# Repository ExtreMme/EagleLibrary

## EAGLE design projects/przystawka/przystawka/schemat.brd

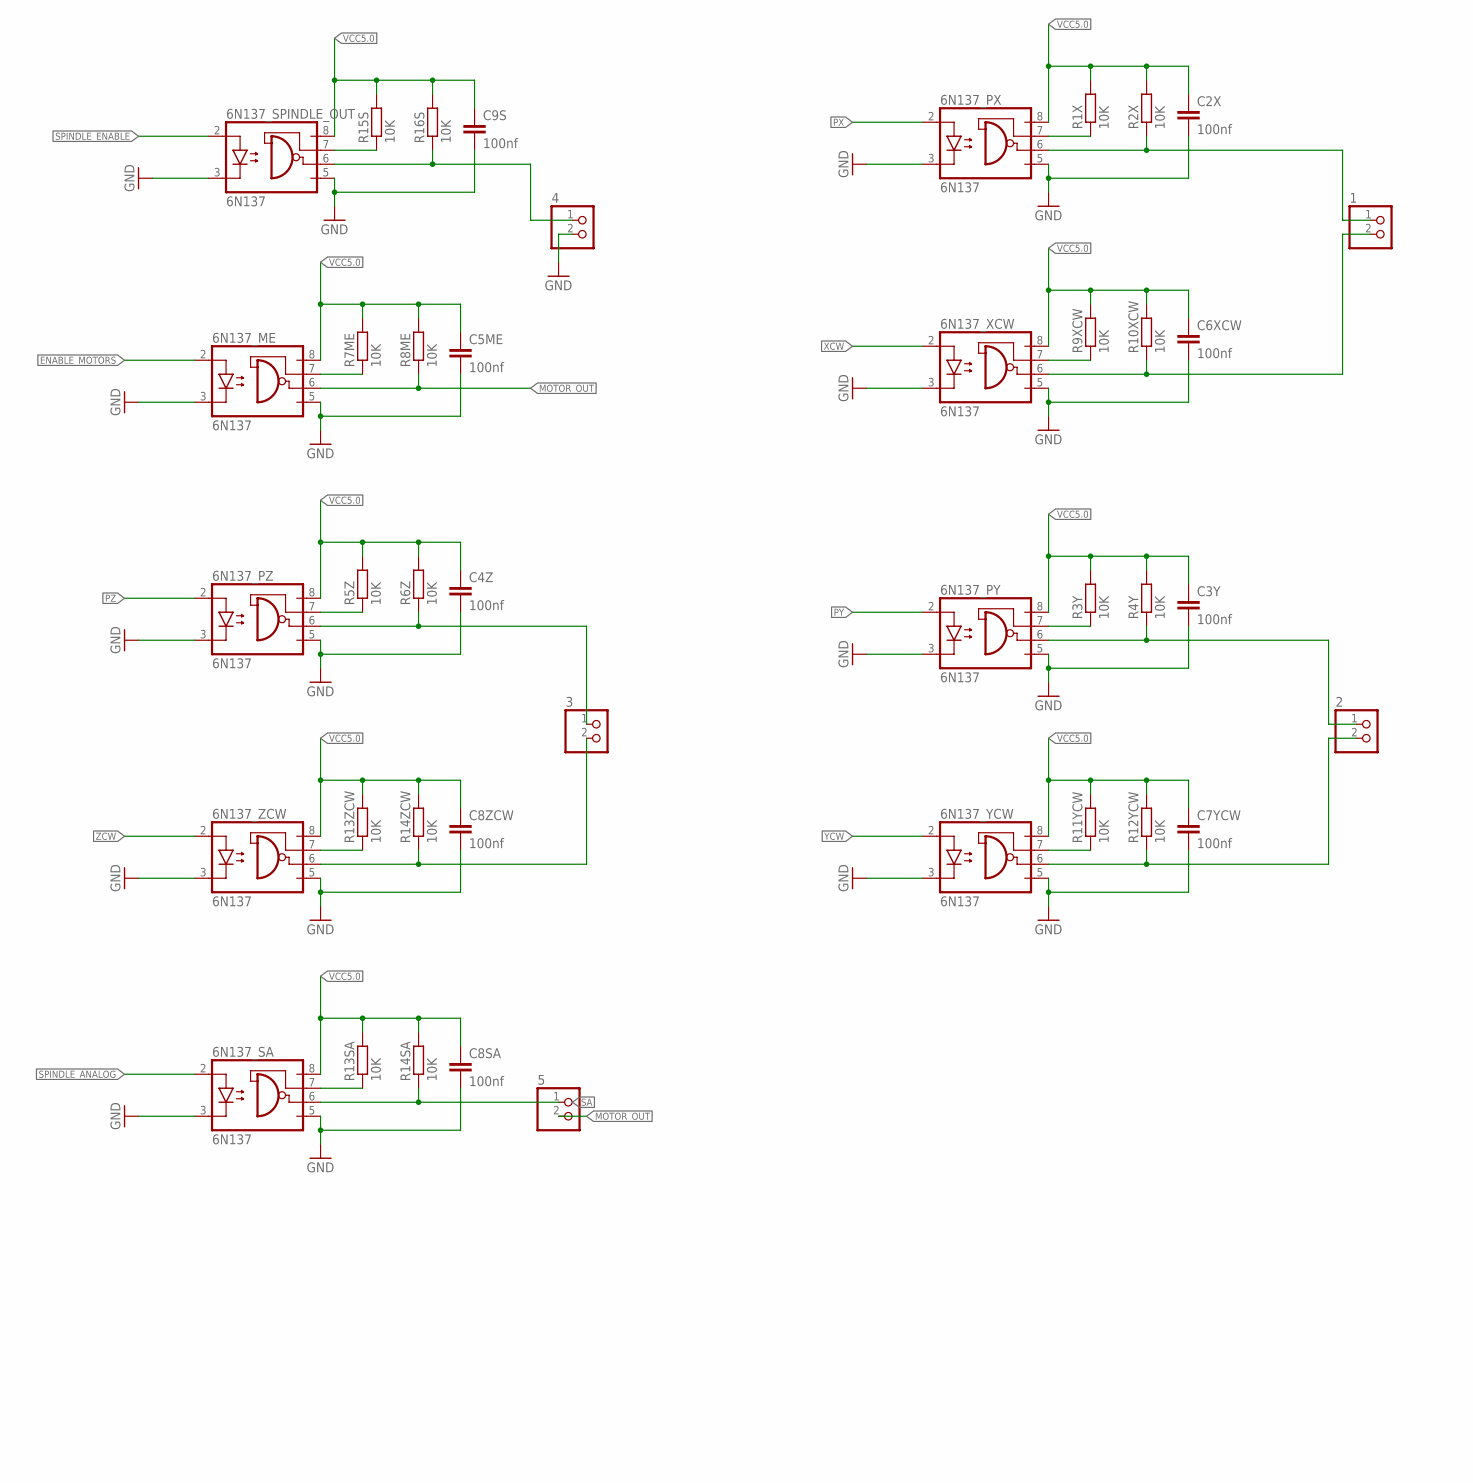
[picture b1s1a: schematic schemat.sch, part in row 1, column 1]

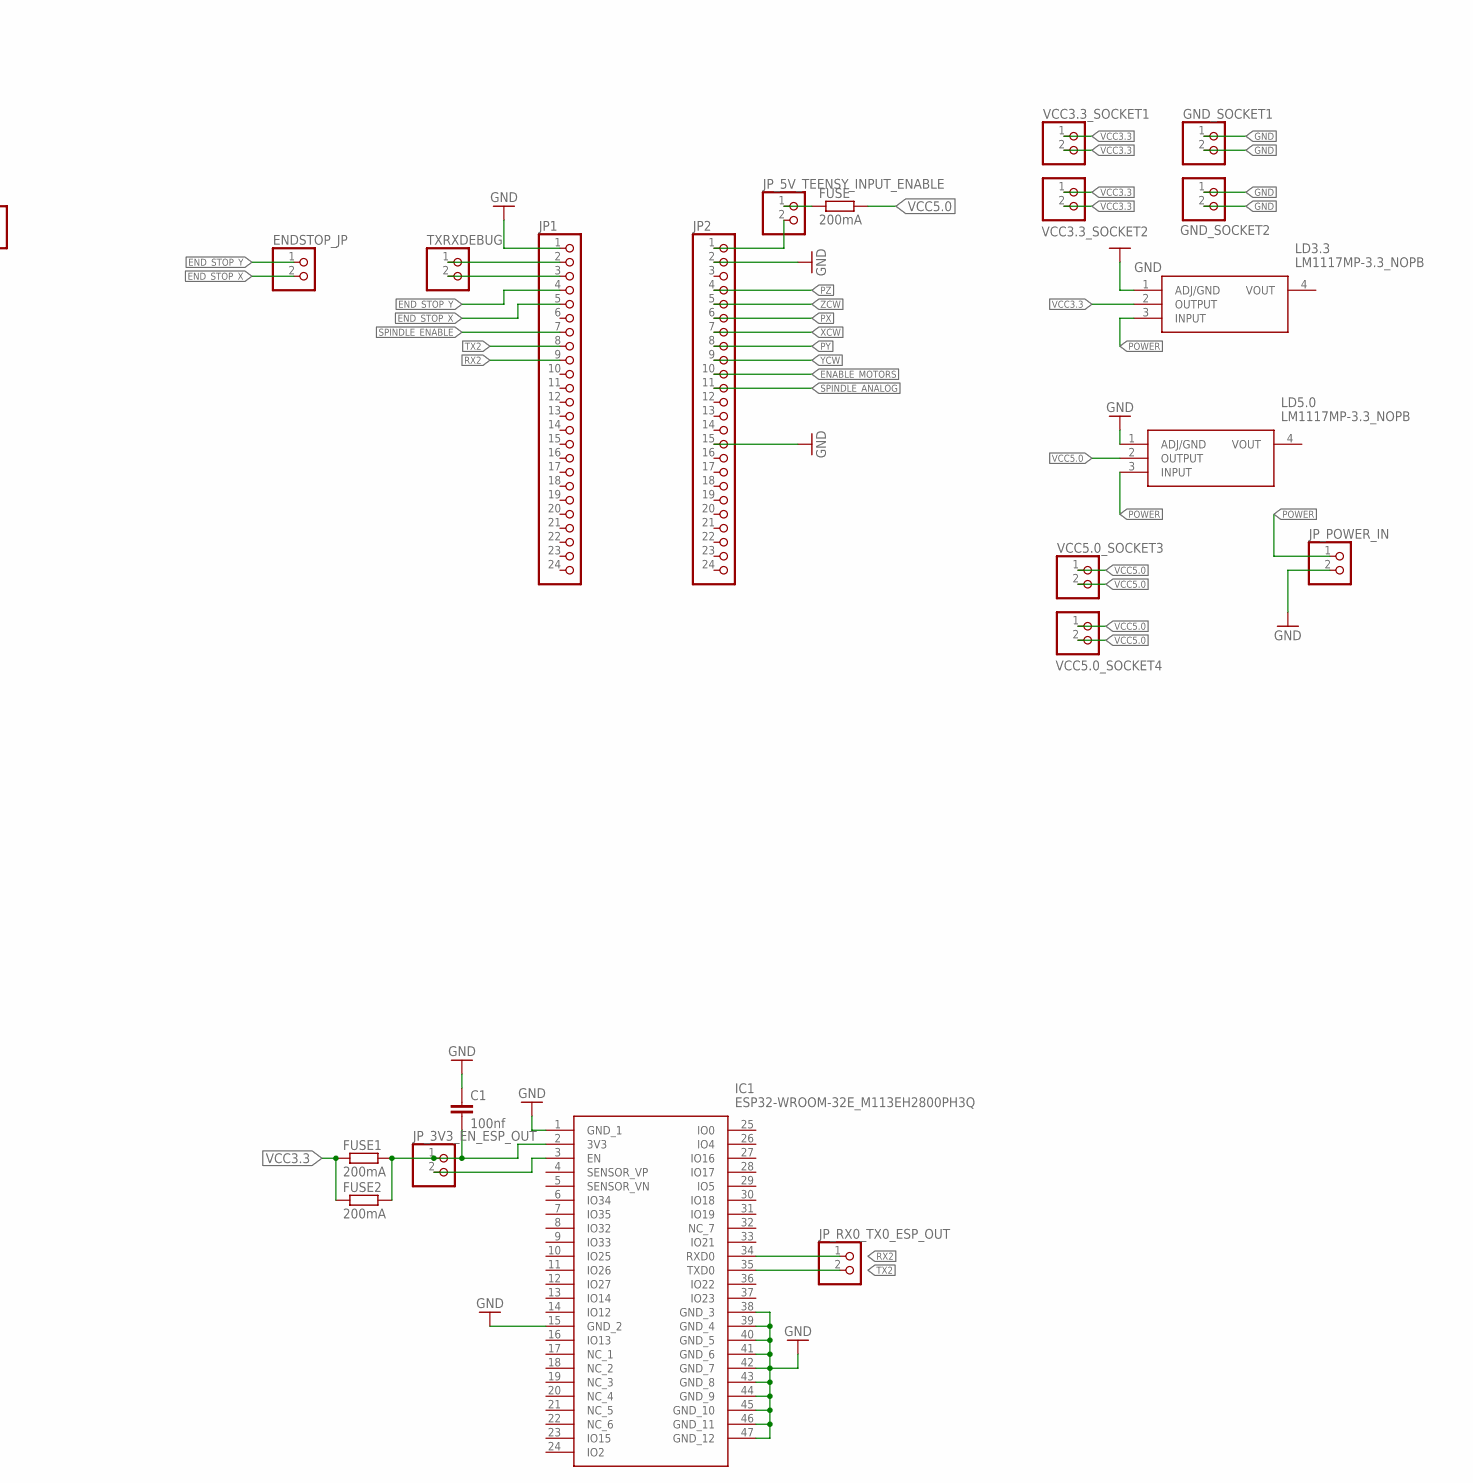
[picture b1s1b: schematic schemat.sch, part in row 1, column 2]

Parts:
1, 2, 3, 4, 5: PINHD-1X2; 1X02
6N137_ME, 6N137_PX, 6N137_PY, 6N137_PZ, 6N137_SA, 6N137_SPINDLE_OUT, 6N137_XCW, 6N137_YCW, 6N137_ZCW: 6N137; DIL08
C1, C2X, C3Y, C4Z, C5ME, C6XCW, C7YCW, C8SA, C8ZCW, C9S: 100nf; C0805
ENDSTOP_JP: PINHD-1X2; 1X02
FUSE, FUSE1, FUSE2: 200mA; R2512
GND_SOCKET1, GND_SOCKET2: PINHD-1X2; 1X02
IC1: ESP32-WROOM-32E_M113EH2800PH3Q; ESP32WROOM32EM113EH2800PH3Q0
JP1, JP2: PINHD-1X24; 1X24
JP_3V3_EN_ESP_OUT, JP_5V_TEENSY_INPUT_ENABLE: PINHD-1X2; 1X02
JP_POWER_IN: PINHD-1X2; 1X02
JP_RX0_TX0_ESP_OUT: PINHD-1X2; 1X02
LD3.3, LD5.0: LM1117MP-3.3_NOPB; SOT230P700X180-4N
R1X, R2X, R3Y, R4Y, R5Z, R6Z, R7ME, R8ME, R9XCW, R10XCW, R11YCW, R12YCW, R13SA, R13ZCW, R14SA, R14ZCW, R15S, R16S: 10K; R0805
TXRXDEBUG: PINHD-1X2; 1X02
VCC3.3_SOCKET1, VCC3.3_SOCKET2, VCC5.0_SOCKET3, VCC5.0_SOCKET4: PINHD-1X2; 1X02

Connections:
ENABLE_MOTORS: 6N137_ME.2 (A), JP2.10
END_STOP_X: ENDSTOP_JP.2, JP1.5
END_STOP_Y: ENDSTOP_JP.1, JP1.4
GND: 4.2, 6N137_ME.3 (C), 6N137_ME.5 (GND), 6N137_PX.3 (C), 6N137_PX.5 (GND), 6N137_PY.3 (C), 6N137_PY.5 (GND), 6N137_PZ.3 (C), 6N137_PZ.5 (GND), 6N137_SA.3 (C), 6N137_SA.5 (GND), 6N137_SPINDLE_OUT.3 (C), 6N137_SPINDLE_OUT.5 (GND), 6N137_XCW.3 (C), 6N137_XCW.5 (GND), 6N137_YCW.3 (C), 6N137_YCW.5 (GND), 6N137_ZCW.3 (C), 6N137_ZCW.5 (GND), C1.1, C2X.2, C3Y.2, C4Z.2, C5ME.2, C6XCW.2, C7YCW.2, C8SA.2, C8ZCW.2, C9S.2, GND_SOCKET1.1, GND_SOCKET1.2, GND_SOCKET2.1, GND_SOCKET2.2, IC1.1 (GND_1), IC1.15 (GND_2), IC1.38 (GND_3), IC1.39 (GND_4), IC1.40 (GND_5), IC1.41 (GND_6), IC1.42 (GND_7), IC1.43 (GND_8), IC1.44 (GND_9), IC1.45 (GND_10), IC1.46 (GND_11), IC1.47 (GND_12), JP1.1, JP2.2, JP2.15, JP_POWER_IN.2, LD3.3.1 (ADJ/GND), LD5.0.1 (ADJ/GND)
MOTOR_OUT: 5.2, 6N137_ME.6 (VO), R8ME.1
unnamed: JP2.1, JP_5V_TEENSY_INPUT_ENABLE.2
unnamed: JP1.2, TXRXDEBUG.1
unnamed: IC1.3 (EN), JP_3V3_EN_ESP_OUT.2
unnamed: JP1.3, TXRXDEBUG.2
unnamed: 6N137_PX.7 (VE), R1X.1
unnamed: 6N137_PY.7 (VE), R3Y.1
unnamed: 6N137_PZ.7 (VE), R5Z.1
unnamed: 6N137_ME.7 (VE), R7ME.1
unnamed: 6N137_SPINDLE_OUT.7 (VE), R15S.1
unnamed: 6N137_XCW.7 (VE), R9XCW.1
unnamed: 6N137_YCW.7 (VE), R11YCW.1
unnamed: 6N137_ZCW.7 (VE), R13ZCW.1
unnamed: FUSE.1, JP_5V_TEENSY_INPUT_ENABLE.1
unnamed: C1.2, FUSE1.2, FUSE2.2, IC1.2 (3V3), JP_3V3_EN_ESP_OUT.1
unnamed: 6N137_SA.7 (VE), R13SA.1
POWER: JP_POWER_IN.1, LD3.3.3 (INPUT), LD5.0.3 (INPUT)
PX: 6N137_PX.2 (A), JP2.6
PX_OUT: 1.1, 6N137_PX.6 (VO), R2X.1
PY: 6N137_PY.2 (A), JP2.8
PY_OUT: 2.1, 6N137_PY.6 (VO), R4Y.1
PZ: 6N137_PZ.2 (A), JP2.4
PZ_OUT: 3.1, 6N137_PZ.6 (VO), R6Z.1
RX2: IC1.34 (RXD0), JP1.9, JP_RX0_TX0_ESP_OUT.1
SA: 5.1, 6N137_SA.6 (VO), R14SA.1
SPINDLE_ANALOG: 6N137_SA.2 (A), JP2.11
SPINDLE_ENABLE: 6N137_SPINDLE_OUT.2 (A), JP1.7
SPINDLE_OUT: 4.1, 6N137_SPINDLE_OUT.6 (VO), R16S.1
TX2: IC1.35 (TXD0), JP1.8, JP_RX0_TX0_ESP_OUT.2
VCC3.3: FUSE1.1, FUSE2.1, LD3.3.2 (OUTPUT), VCC3.3_SOCKET1.1, VCC3.3_SOCKET1.2, VCC3.3_SOCKET2.1, VCC3.3_SOCKET2.2
VCC5.0: 6N137_ME.8 (VCC), 6N137_PX.8 (VCC), 6N137_PY.8 (VCC), 6N137_PZ.8 (VCC), 6N137_SA.8 (VCC), 6N137_SPINDLE_OUT.8 (VCC), 6N137_XCW.8 (VCC), 6N137_YCW.8 (VCC), 6N137_ZCW.8 (VCC), C2X.1, C3Y.1, C4Z.1, C5ME.1, C6XCW.1, C7YCW.1, C8SA.1, C8ZCW.1, C9S.1, FUSE.2, LD5.0.2 (OUTPUT), R1X.2, R2X.2, R3Y.2, R4Y.2, R5Z.2, R6Z.2, R7ME.2, R8ME.2, R9XCW.2, R10XCW.2, R11YCW.2, R12YCW.2, R13SA.2, R13ZCW.2, R14SA.2, R14ZCW.2, R15S.2, R16S.2, VCC5.0_SOCKET3.1, VCC5.0_SOCKET3.2, VCC5.0_SOCKET4.1, VCC5.0_SOCKET4.2
XCW: 6N137_XCW.2 (A), JP2.7
XCW_OUT: 1.2, 6N137_XCW.6 (VO), R10XCW.1
YCW: 6N137_YCW.2 (A), JP2.9
YCW_OUT: 2.2, 6N137_YCW.6 (VO), R12YCW.1
ZCW: 6N137_ZCW.2 (A), JP2.5
ZCW_OUT: 3.2, 6N137_ZCW.6 (VO), R14ZCW.1

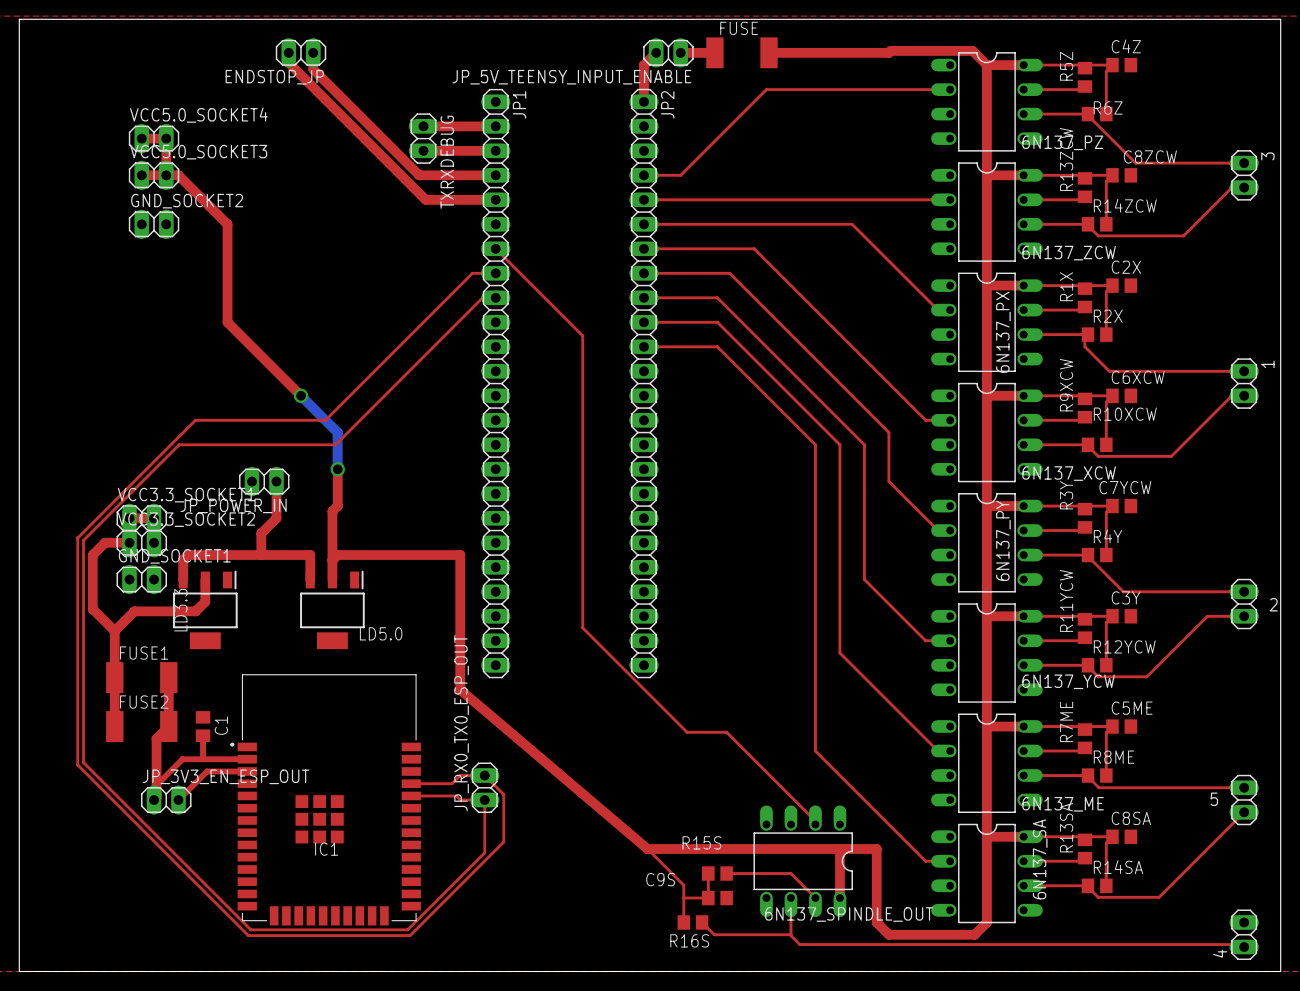
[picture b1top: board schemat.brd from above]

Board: 2 copper layers, 130.8 x 98.7 mm, 62 parts (0 on the bottom side), 41 nets.

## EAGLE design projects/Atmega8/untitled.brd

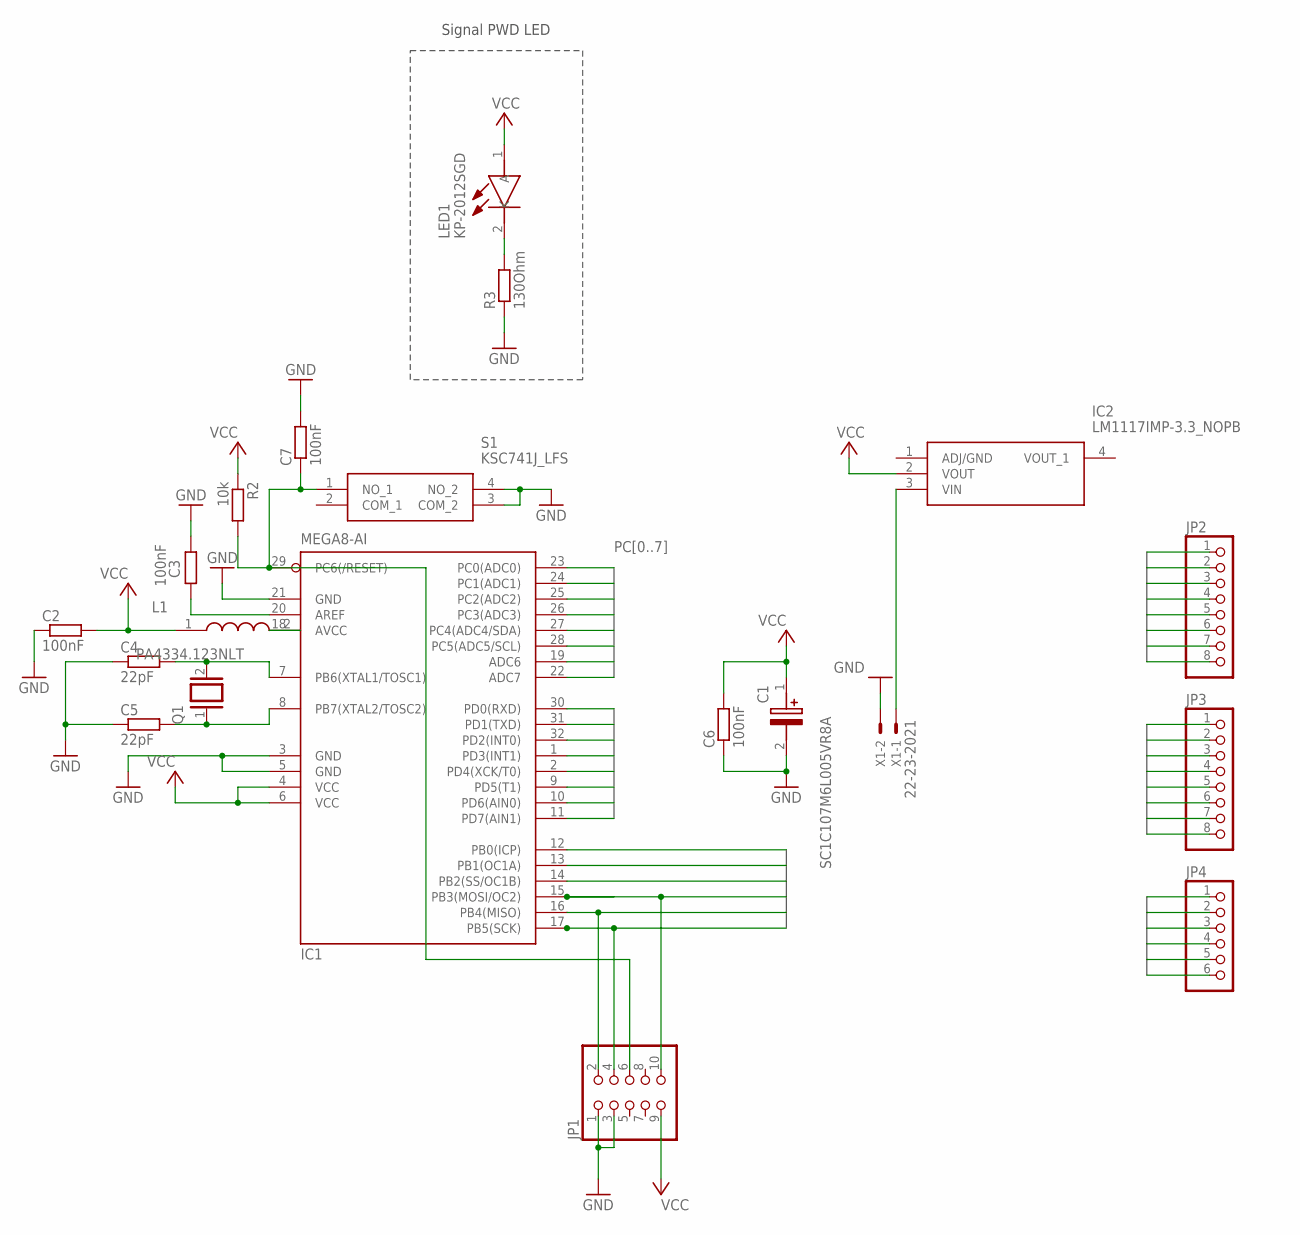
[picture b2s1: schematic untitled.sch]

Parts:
C1: SC1C107M6L005VR8A; CAPAE660X560N
C2, C3, C6, C7: 100nF; R0805
C4, C5: 22pF; R0805
IC1: MEGA8-AI; TQFP32-08
IC2: LM1117IMP-3.3_NOPB; SOT230P700X180-4N
JP1: PINHD-2X5; 2X05
JP2, JP3: PINHD-1X8; 1X08
JP4: PINHD-1X6; 1X06
L1: PA4334.123NLT; PA4334123NLT
LED1: KP-2012SGD; KP2012SGD
Q1: XTAL/S; QS
R2: 10k; R0805
R3: 130Ohm; R0805
S1: KSC741J_LFS; KSC821JOLLFS
X1: 22-23-2021

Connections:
ADJ/GND: IC2.1 (ADJ/GND)
GND: C1.2 (-), C2.1, C3.1, C4.1, C5.1, C6.1, C7.2, IC1.3 (GND), IC1.5 (GND), IC1.21 (GND), JP1.1, JP1.3, R3.1, S1.3 (COM_2), S1.4 (NO_2), X1.2
unnamed: C7.1, IC1.29 (PC6(/RESET)), JP1.6, R2.2, S1.1 (NO_1)
unnamed: IC1.18 (AVCC), L1.2
unnamed: C3.2, IC1.20 (AREF)
unnamed: C4.2, IC1.7 (PB6(XTAL1/TOSC1)), Q1.2
unnamed: C5.2, IC1.8 (PB7(XTAL2/TOSC2)), Q1.1
unnamed: LED1.2 (K), R3.2
unnamed: IC2.3 (VIN), X1.1
PB0: IC1.12 (PB0(ICP)), JP4.1
PB1: IC1.13 (PB1(OC1A)), JP4.2
PB2: IC1.14 (PB2(SS/OC1B)), JP4.3
PB3: IC1.15 (PB3(MOSI/OC2)), JP1.10, JP4.4
PB4: IC1.16 (PB4(MISO)), JP1.2, JP4.5
PB5: IC1.17 (PB5(SCK)), JP1.4, JP4.6
PC0: IC1.23 (PC0(ADC0)), JP2.1
PC1: IC1.24 (PC1(ADC1)), JP2.2
PC2: IC1.25 (PC2(ADC2)), JP2.3
PC3: IC1.26 (PC3(ADC3)), JP2.4
PC4: IC1.27 (PC4(ADC4/SDA)), JP2.5
PC5: IC1.28 (PC5(ADC5/SCL)), JP2.6
PC6: IC1.19 (ADC6), JP2.7
PC7: IC1.22 (ADC7), JP2.8
PD0: IC1.30 (PD0(RXD)), JP3.1
PD1: IC1.31 (PD1(TXD)), JP3.2
PD2: IC1.32 (PD2(INT0)), JP3.3
PD3: IC1.1 (PD3(INT1)), JP3.4
PD4: IC1.2 (PD4(XCK/T0)), JP3.5
PD5: IC1.9 (PD5(T1)), JP3.6
PD6: IC1.10 (PD6(AIN0)), JP3.7
PD7: IC1.11 (PD7(AIN1)), JP3.8
VCC: C1.1 (+), C2.2, C6.2, IC1.4 (VCC), IC1.6 (VCC), IC2.2 (VOUT), JP1.9, L1.1, LED1.1 (A), R2.1

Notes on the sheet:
Signal PWD LED

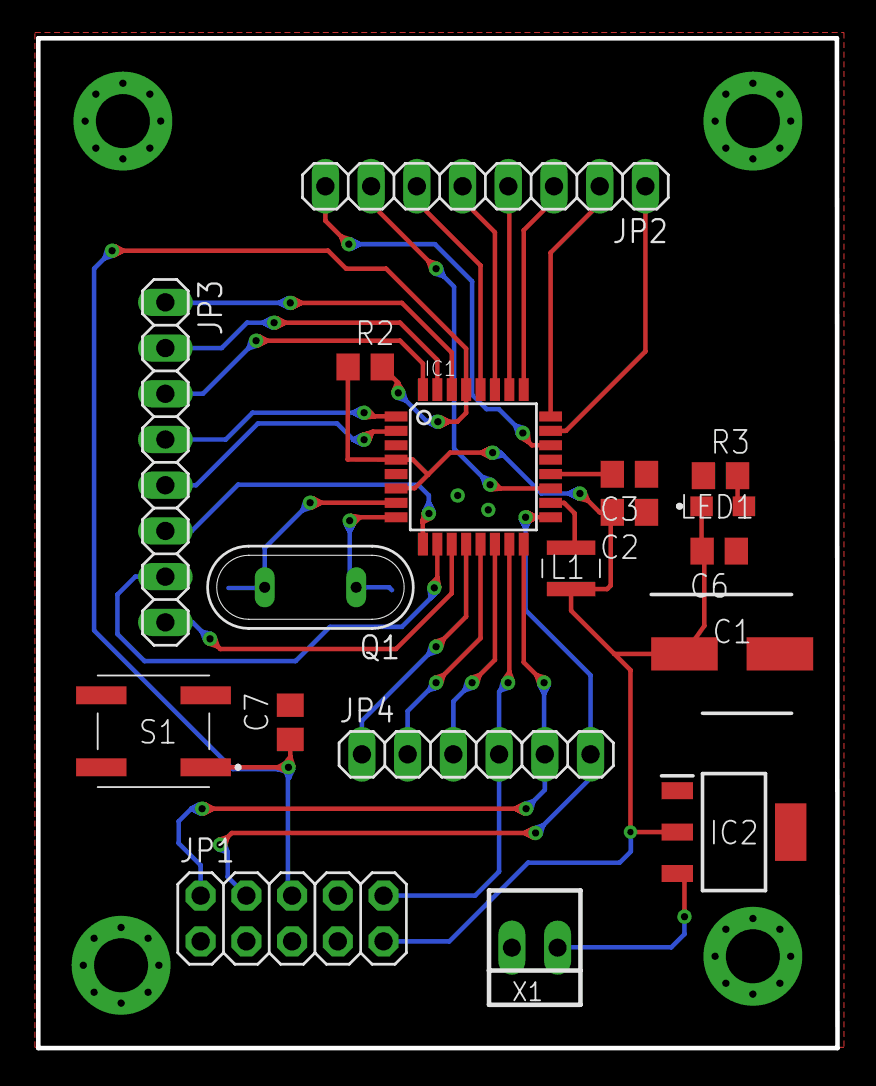
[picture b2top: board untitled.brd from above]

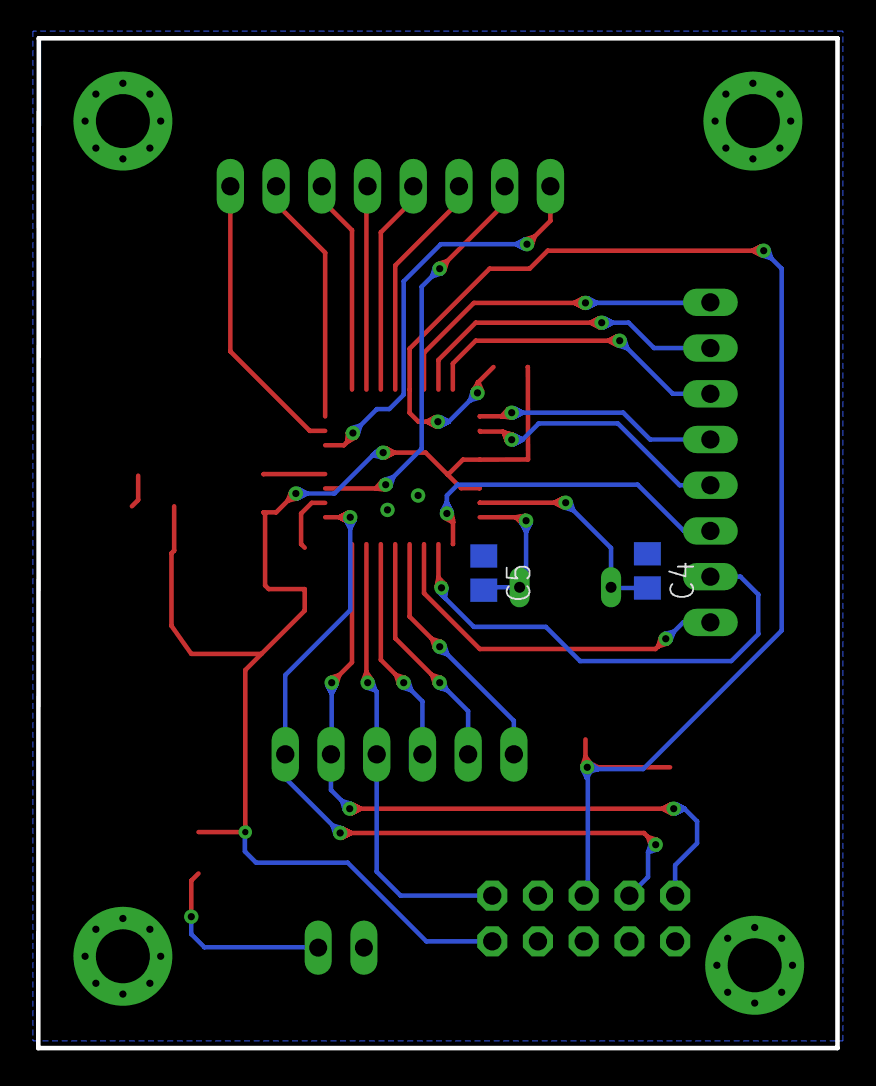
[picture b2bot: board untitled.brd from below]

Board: 2 copper layers, 44.4 x 56.1 mm, 20 parts (2 on the bottom side), 31 nets.

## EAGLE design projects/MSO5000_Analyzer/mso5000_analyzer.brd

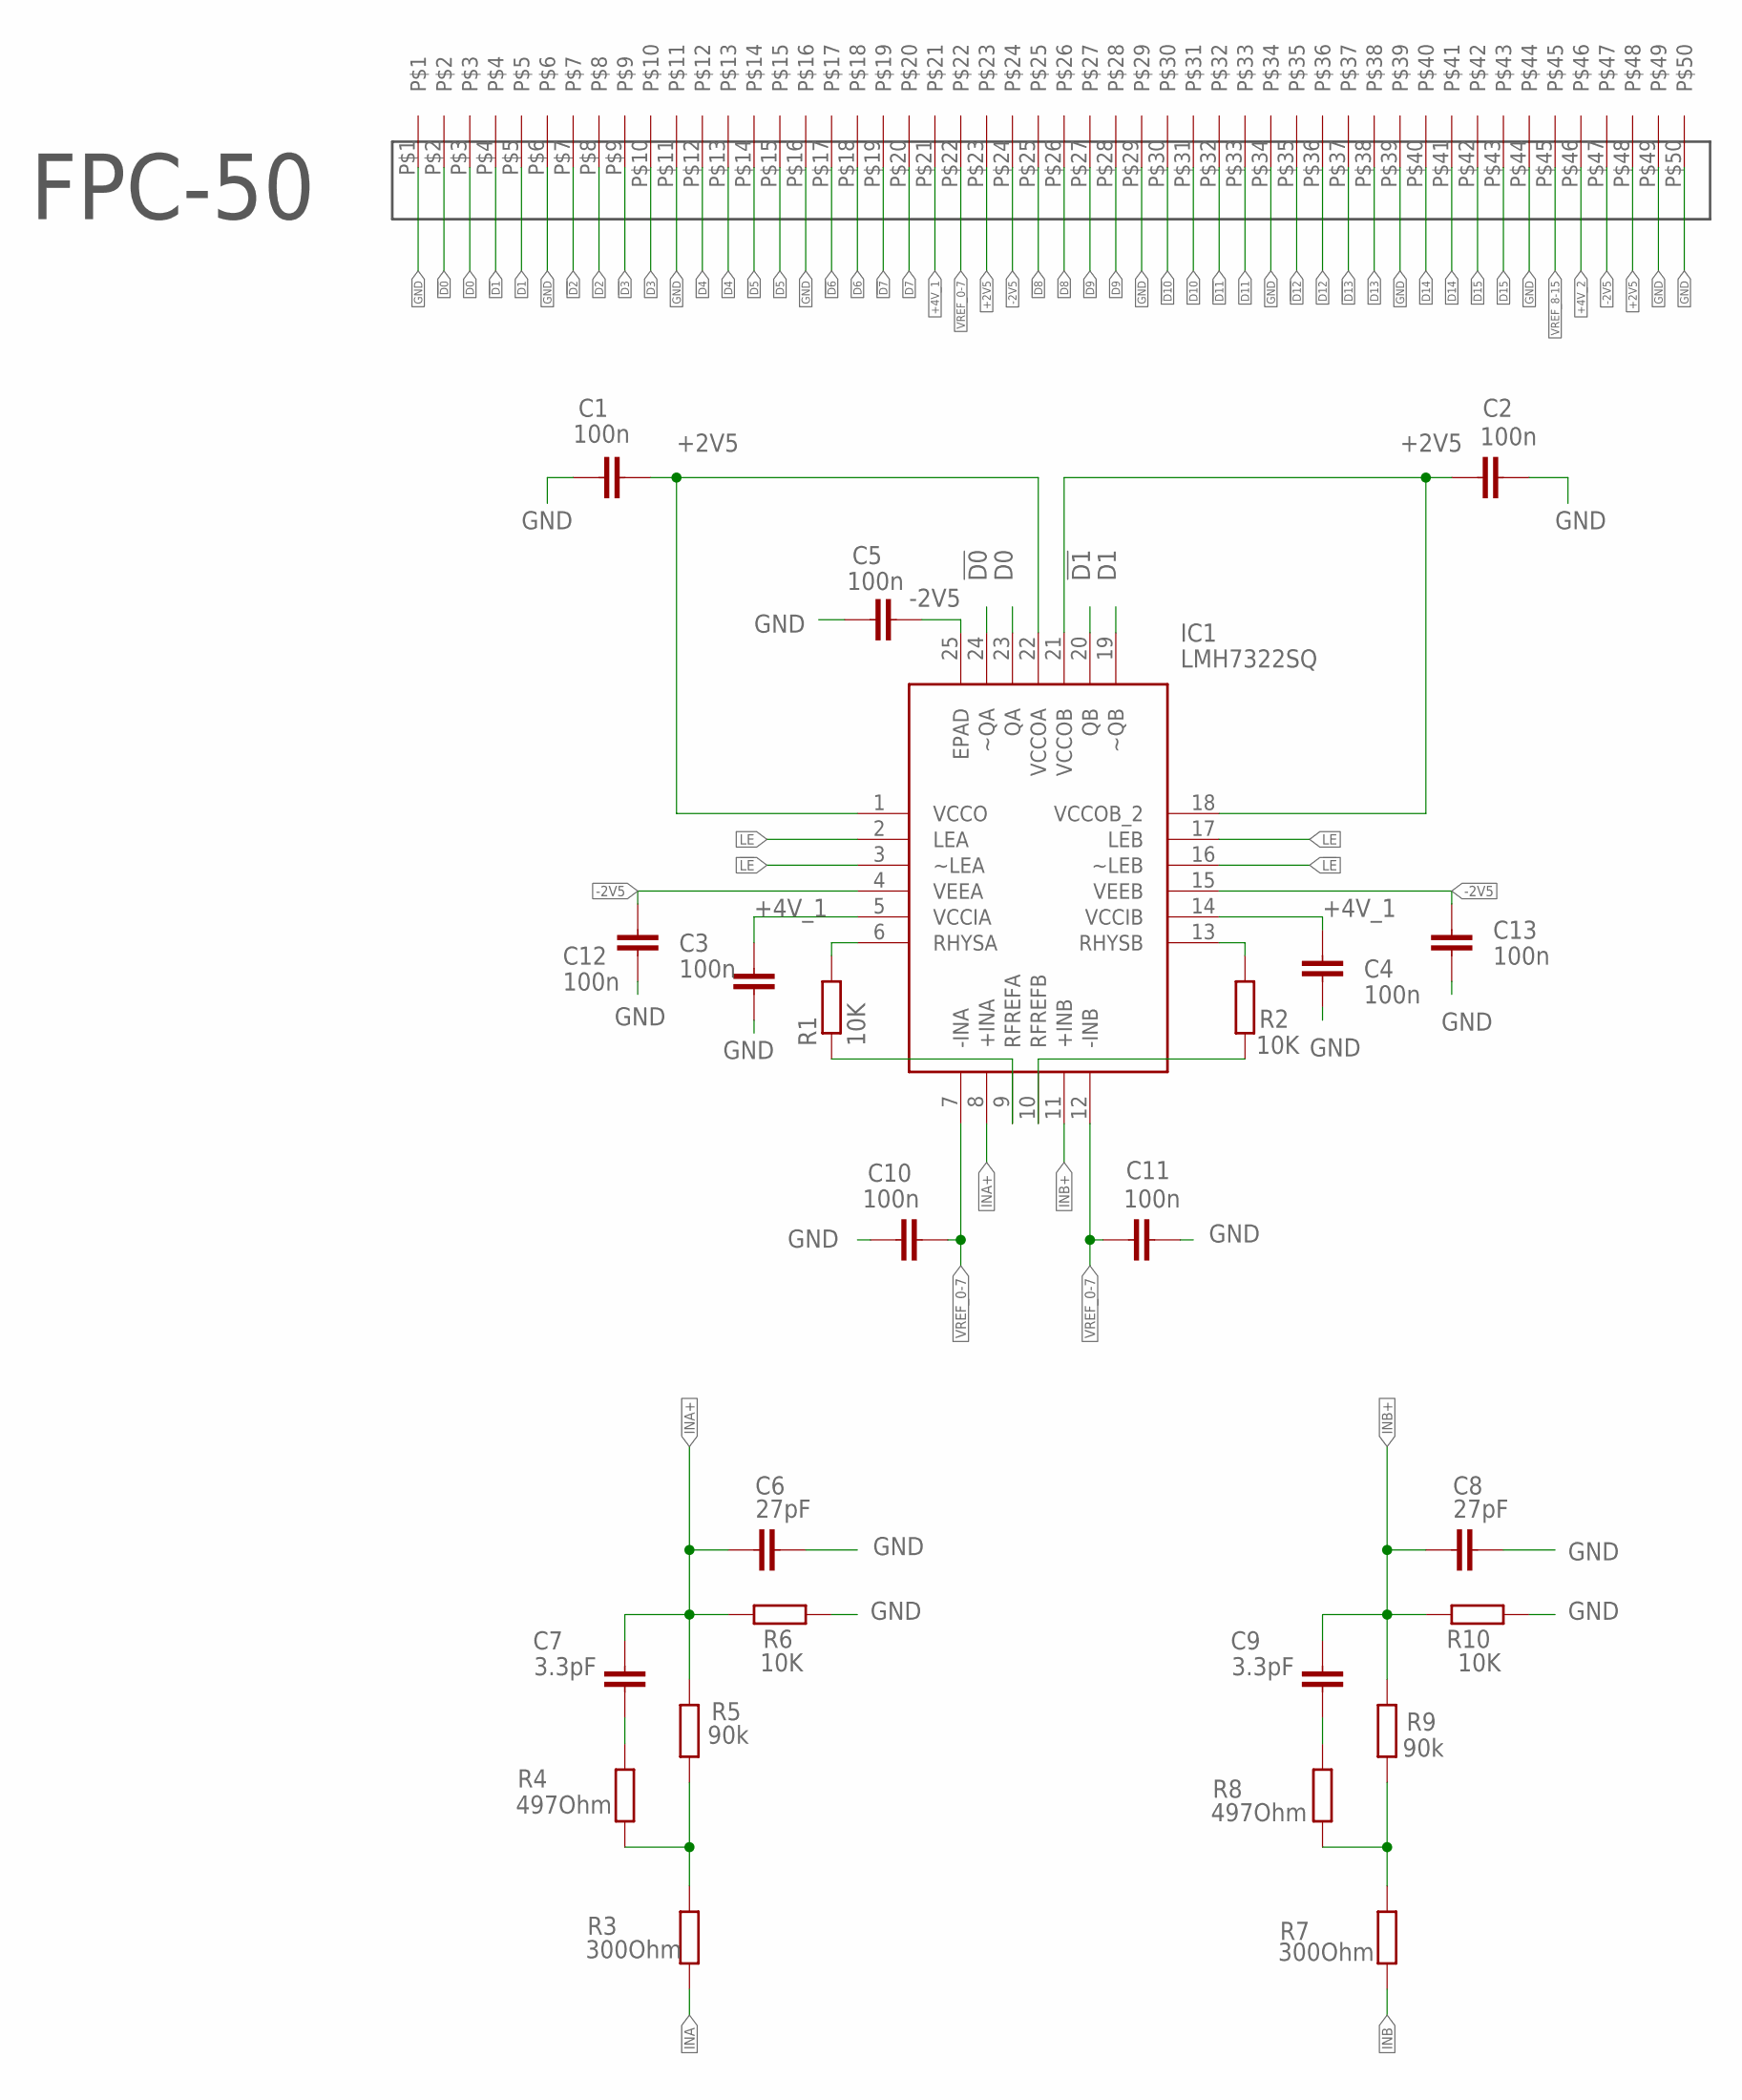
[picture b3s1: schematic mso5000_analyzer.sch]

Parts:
C1, C2, C3, C4, C5, C10, C11, C12, C13: 100n; C0805
C6, C8: 27pF; C0805
C7, C9: 3.3pF; C0805
FPC-50: ZIFF-050
IC1: LMH7322SQ; QFN50P400X400X80-25N
R1, R2, R6, R10: 10K; R0805
R3, R7: 300Ohm; R0805
R4, R8: 497Ohm; R0805
R5, R9: 90k; R0805

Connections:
!D0: FPC-50.P$2, IC1.24 (~QA)
!D1: FPC-50.P$4, IC1.20 (QB)
!D2: FPC-50.P$7
!D3: FPC-50.P$9
!D4: FPC-50.P$12
!D5: FPC-50.P$14
!D6: FPC-50.P$17
!D7: FPC-50.P$19
!D8: FPC-50.P$25
!D9: FPC-50.P$27
!D10: FPC-50.P$30
!D11: FPC-50.P$32
!D12: FPC-50.P$35
!D13: FPC-50.P$37
!D14: FPC-50.P$40
!D15: FPC-50.P$42
!LE: IC1.3 (~LEA), IC1.16 (~LEB)
+2V5: C1.1, C2.2, FPC-50.P$23, FPC-50.P$48, IC1.1 (VCCO), IC1.18 (VCCOB_2), IC1.21 (VCCOB), IC1.22 (VCCOA)
+4V_1: C3.1, C4.1, FPC-50.P$21, IC1.5 (VCCIA), IC1.14 (VCCIB)
+4V_2: FPC-50.P$46
-2V5: C5.1, C12.1, C13.1, FPC-50.P$24, FPC-50.P$47, IC1.4 (VEEA), IC1.15 (VEEB), IC1.25 (EPAD)
D0: FPC-50.P$3, IC1.23 (QA)
D1: FPC-50.P$5, IC1.19 (~QB)
D2: FPC-50.P$8
D3: FPC-50.P$10
D4: FPC-50.P$13
D5: FPC-50.P$15
D6: FPC-50.P$18
D7: FPC-50.P$20
D8: FPC-50.P$26
D9: FPC-50.P$28
D10: FPC-50.P$31
D11: FPC-50.P$33
D12: FPC-50.P$36
D13: FPC-50.P$38
D14: FPC-50.P$41
D15: FPC-50.P$43
GND: C1.2, C2.1, C3.2, C4.2, C5.2, C6.2, C8.2, C10.1, C11.2, C12.2, C13.2, FPC-50.P$1, FPC-50.P$6, FPC-50.P$11, FPC-50.P$16, FPC-50.P$29, FPC-50.P$34, FPC-50.P$39, FPC-50.P$44, FPC-50.P$49, FPC-50.P$50, R6.1, R10.1
INA: R3.1
INA+: C6.1, C7.2, IC1.8 (+INA), R5.2, R6.2
INB: R7.1
INB+: C8.1, C9.2, IC1.11 (+INB), R9.2, R10.2
LE: IC1.2 (LEA), IC1.17 (LEB)
unnamed: IC1.10 (RFREFB), R2.1
unnamed: R3.2, R4.1, R5.1
unnamed: IC1.6 (RHYSA), R1.2
unnamed: IC1.9 (RFREFA), R1.1
unnamed: IC1.13 (RHYSB), R2.2
unnamed: C7.1, R4.2
unnamed: R7.2, R8.1, R9.1
unnamed: C9.1, R8.2
VREF_0-7: C10.2, C11.1, FPC-50.P$22, IC1.7 (-INA), IC1.12 (-INB)
VREF_8-15: FPC-50.P$45

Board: 2 copper layers, 25 parts (0 on the bottom side), 21 nets, no tracks yet.

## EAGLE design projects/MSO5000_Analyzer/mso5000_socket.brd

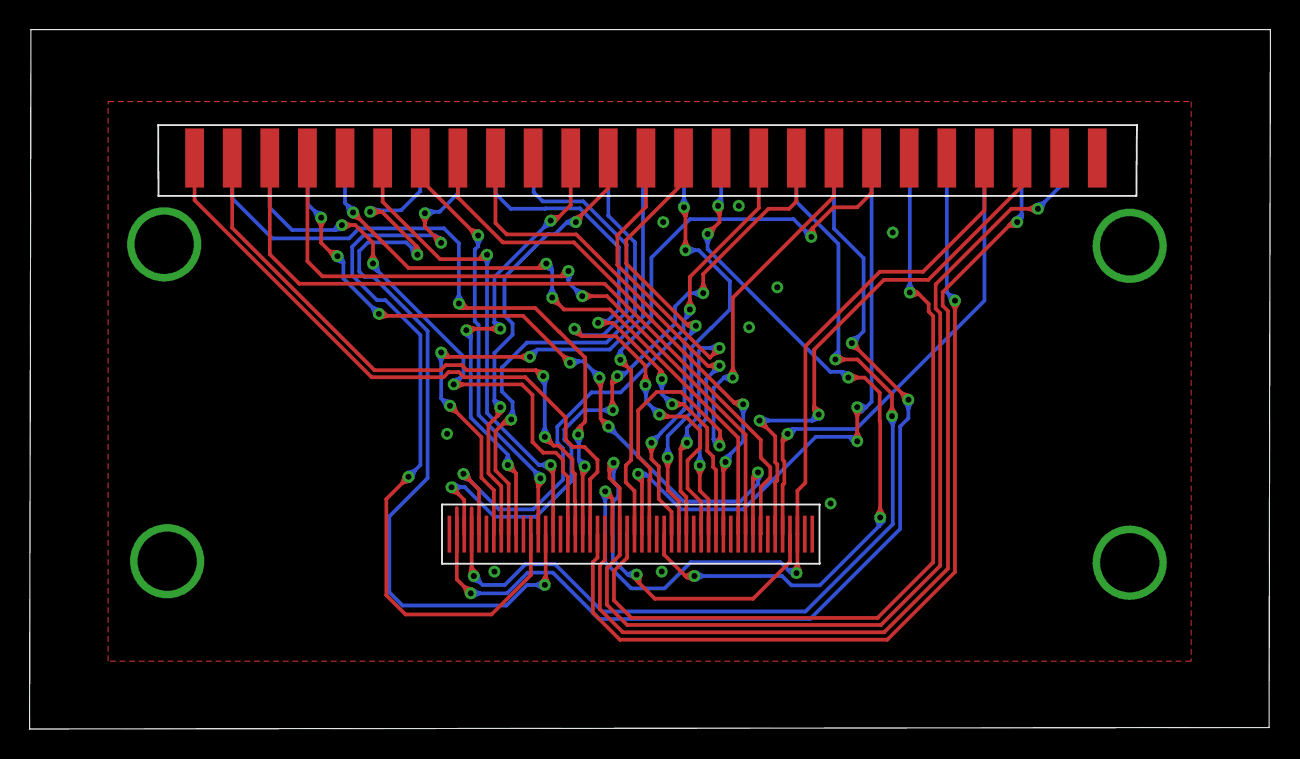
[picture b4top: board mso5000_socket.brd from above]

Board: 2 copper layers, 83.8 x 47.2 mm, 3 parts (1 on the bottom side), 39 nets.

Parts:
IDC_BOTTOM: 1X25_IDC_PADS
IDC_TOP: 1X25_IDC_PADS
U$3: ZIFF-050

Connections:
!D0: IDC_BOTTOM.P$18, U$3.P$2
!D1: IDC_BOTTOM.P$17, U$3.P$4
!D2: IDC_BOTTOM.P$13, U$3.P$7
!D3: IDC_BOTTOM.P$12, U$3.P$9
!D4: IDC_BOTTOM.P$8, U$3.P$12
!D5: IDC_BOTTOM.P$7, U$3.P$14
!D6: IDC_BOTTOM.P$3, U$3.P$17
!D7: IDC_BOTTOM.P$2, U$3.P$19
!D8: IDC_BOTTOM.P$20, U$3.P$25
!D9: IDC_BOTTOM.P$19, U$3.P$27
!D10: IDC_BOTTOM.P$15, U$3.P$30
!D11: IDC_BOTTOM.P$14, U$3.P$32
!D12: IDC_BOTTOM.P$10, U$3.P$35
!D13: IDC_BOTTOM.P$9, U$3.P$37
!D14: IDC_BOTTOM.P$5, U$3.P$40
!D15: IDC_BOTTOM.P$4, U$3.P$42
+2V5: IDC_TOP.P$22, U$3.P$23, U$3.P$48
+4V_1: IDC_BOTTOM.P$21, U$3.P$21
+4V_2: IDC_BOTTOM.P$22, U$3.P$46
-2V5: IDC_BOTTOM.P$24, U$3.P$24, U$3.P$47
D0: IDC_TOP.P$17, U$3.P$3
D1: IDC_TOP.P$16, U$3.P$5
D2: IDC_TOP.P$12, U$3.P$8
D3: IDC_TOP.P$11, U$3.P$10
D4: IDC_TOP.P$7, U$3.P$13
D5: IDC_TOP.P$6, U$3.P$15
D6: IDC_TOP.P$2, U$3.P$18
D7: IDC_TOP.P$1, U$3.P$20
D8: IDC_TOP.P$19, U$3.P$26
D9: IDC_TOP.P$18, U$3.P$28
D10: IDC_TOP.P$14, U$3.P$31
D11: IDC_TOP.P$13, U$3.P$33
D12: IDC_TOP.P$9, U$3.P$36
D13: IDC_TOP.P$8, U$3.P$38
D14: IDC_TOP.P$4, U$3.P$41
D15: IDC_TOP.P$3, U$3.P$43
GND: IDC_BOTTOM.P$1, IDC_BOTTOM.P$6, IDC_BOTTOM.P$11, IDC_BOTTOM.P$16, IDC_BOTTOM.P$25, IDC_TOP.P$5, IDC_TOP.P$10, IDC_TOP.P$15, IDC_TOP.P$20, IDC_TOP.P$21, IDC_TOP.P$24, IDC_TOP.P$25, U$3.P$1, U$3.P$6, U$3.P$11, U$3.P$16, U$3.P$29, U$3.P$34, U$3.P$39, U$3.P$44, U$3.P$49, U$3.P$50
VREF_0-7: IDC_BOTTOM.P$23, U$3.P$22
VREF_8-15: IDC_TOP.P$23, U$3.P$45

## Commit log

2020-09-21 Add Eagle library
2020-09-21 Update eagle lib to current version
2020-09-21 remove old files
2020-09-21 Add updates files
2020-09-21 Deleted files
2020-09-21 Editing board
2020-09-21 Editing Area Top and Bottom. Adding extra calibration point's
2020-09-30 Add gcode drill file from flatcam
2021-01-28 Add ESP32-WROOM lib and LDO regulators
2021-01-28 Editing project teensy4.1 cnc board
2021-01-29 Update schemat and board
